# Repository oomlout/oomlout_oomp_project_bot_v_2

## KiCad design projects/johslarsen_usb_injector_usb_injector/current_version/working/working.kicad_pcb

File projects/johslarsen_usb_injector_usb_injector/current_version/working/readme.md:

# usb_injector
 
## summary 
* id: johslarsen_usb_injector_usb_injector
* user: johslarsen
* name: usb_injector
* board: usb_injector
* repo: https://github.com/johslarsen/usb_injector
* src_file_repo_kicad_pcb: usb_injector.kicad_pcb
* src_file_repo_kicad_pcb_link: https://github.com/johslarsen/usb_injector/tree/master/usb_injector.kicad_pcb

* src_file_repo_sch: usb_injector.sch
* src_file_repo_sch_link: https://github.com/johslarsen/usb_injector/tree/master/usb_injector.sch
* full details link: https://github.com/oomlout/oomlout_oomp_project_bot_v_2/tree/main/projects/johslarsen_usb_injector_usb_injector/current_version/working

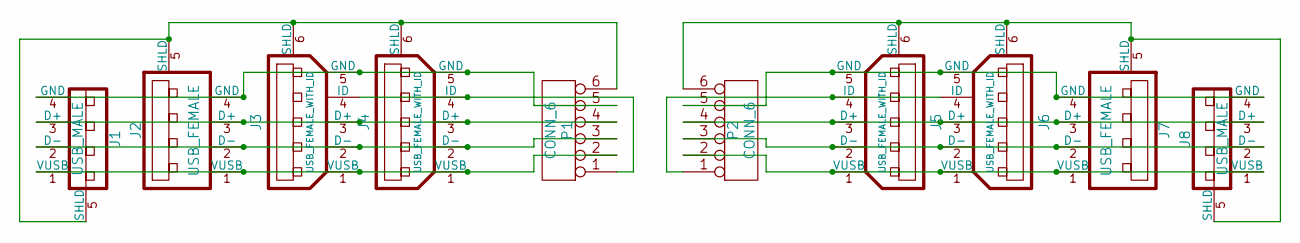
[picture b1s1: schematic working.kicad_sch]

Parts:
J1, J8: USB_MALE
J2, J7: USB_FEMALE
J3, J4, J5, J6: USB_FEMALE_WITH_ID
P1, P2: CONN_6

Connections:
unnamed: J1.1 (VUSB), J2.1 (VUSB), J3.1 (VUSB), J4.1 (VUSB), P1.2
unnamed: J1.2 (D-), J2.2 (D-), J3.2 (D-), J4.2 (D-), P1.3
unnamed: J1.3 (D+), J2.3 (D+), J3.3 (D+), J4.3 (D+), P1.4
unnamed: J1.4 (GND), J2.4 (GND), J3.5 (GND), J4.5 (GND), P1.5
unnamed: J1.5 (SHLD), J2.5 (SHLD), J3.6 (SHLD), J4.6 (SHLD), P1.6
unnamed: J3.4 (ID), J4.4 (ID), P1.1
unnamed: J5.1 (VUSB), J6.1 (VUSB), J7.1 (VUSB), J8.1 (VUSB), P2.2
unnamed: J5.2 (D-), J6.2 (D-), J7.2 (D-), J8.2 (D-), P2.3
unnamed: J5.3 (D+), J6.3 (D+), J7.3 (D+), J8.3 (D+), P2.4
unnamed: J5.4 (ID), J6.4 (ID), P2.1
unnamed: J5.5 (GND), J6.5 (GND), J7.4 (GND), J8.4 (GND), P2.5
unnamed: J5.6 (SHLD), J6.6 (SHLD), J7.5 (SHLD), J8.5 (SHLD), P2.6

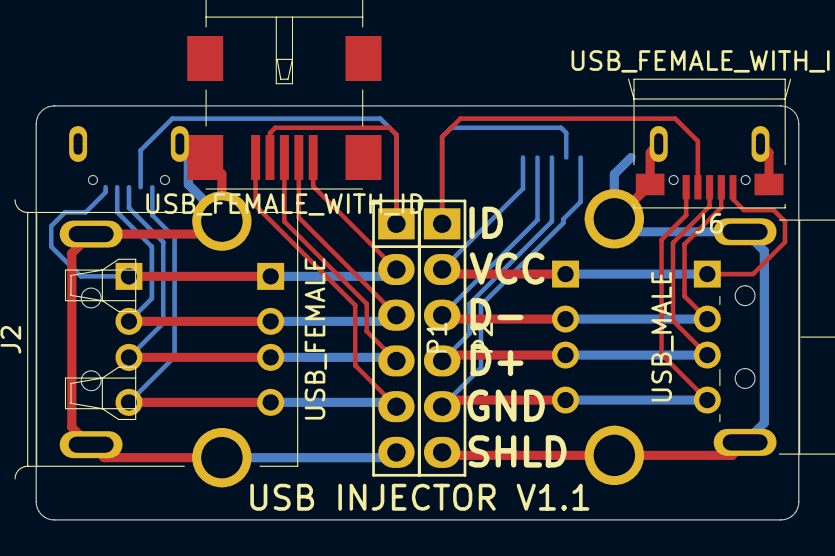
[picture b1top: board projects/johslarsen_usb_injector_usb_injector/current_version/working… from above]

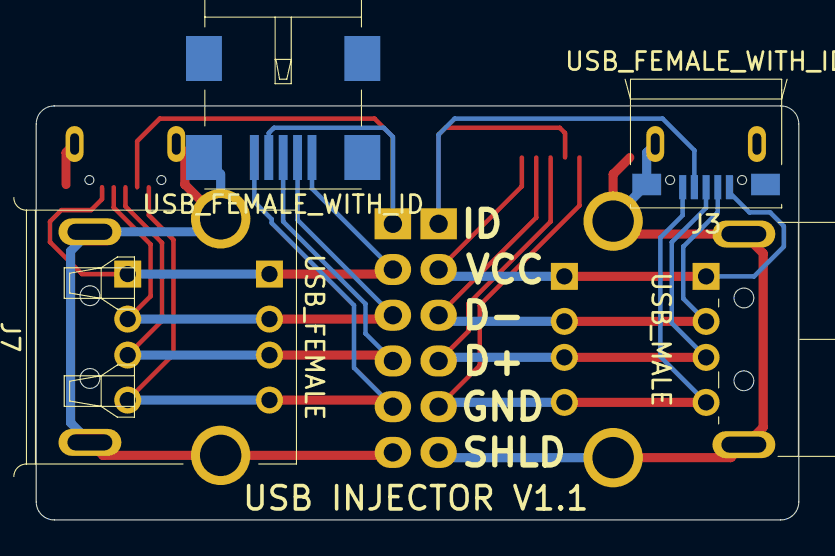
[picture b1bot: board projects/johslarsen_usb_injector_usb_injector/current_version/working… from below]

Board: 2 copper layers, 42.4 x 23.0 mm, 10 parts (4 on the bottom side), 12 nets.

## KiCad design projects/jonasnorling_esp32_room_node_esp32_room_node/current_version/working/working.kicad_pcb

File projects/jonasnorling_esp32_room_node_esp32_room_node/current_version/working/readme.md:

# esp32_room_node
 
## summary 
* id: jonasnorling_esp32_room_node_esp32_room_node
* user: jonasnorling
* name: esp32_room_node
* board: esp32_room_node
* repo: https://github.com/JonasNorling/esp32_room_node
* src_file_repo_kicad_pcb: hw/esp32_room_node.kicad_pcb
* src_file_repo_kicad_pcb_link: https://github.com/JonasNorling/esp32_room_node/tree/main/hw/esp32_room_node.kicad_pcb

* src_file_repo_sch: hw/esp32_room_node.sch
* src_file_repo_sch_link: https://github.com/JonasNorling/esp32_room_node/tree/main/hw/esp32_room_node.sch
* full details link: https://github.com/oomlout/oomlout_oomp_project_bot_v_2/tree/main/projects/jonasnorling_esp32_room_node_esp32_room_node/current_version/working

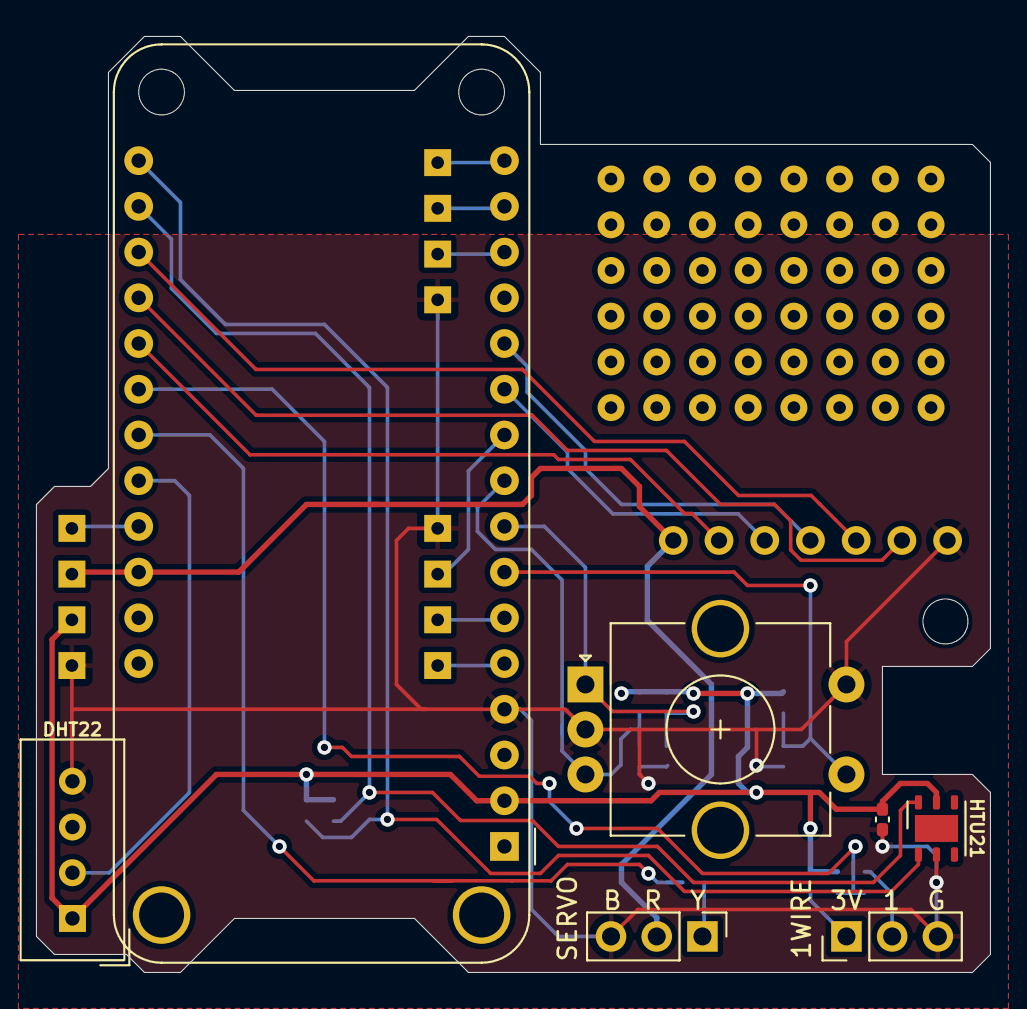
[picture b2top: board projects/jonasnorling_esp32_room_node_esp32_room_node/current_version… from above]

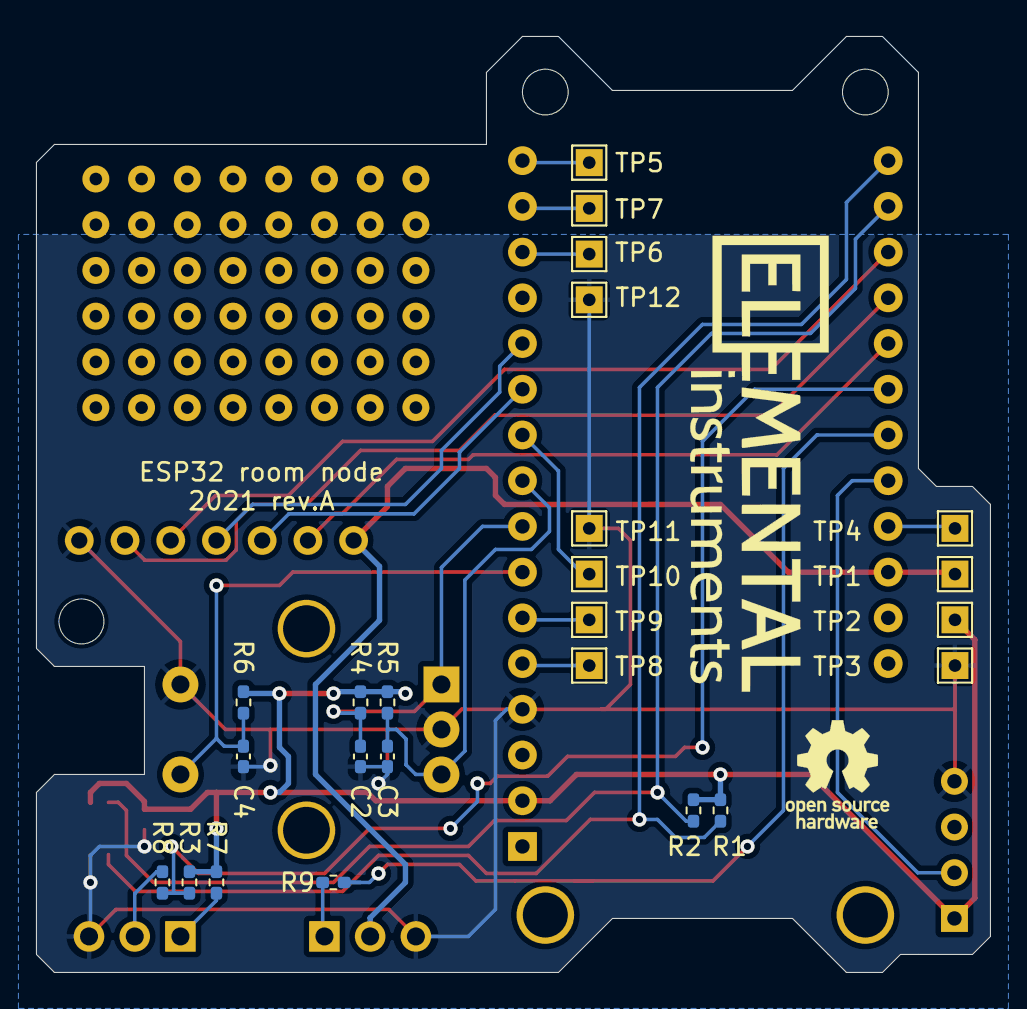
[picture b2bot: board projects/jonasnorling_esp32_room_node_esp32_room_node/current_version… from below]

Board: 2 copper layers, 53.0 x 52.0 mm, 37 parts (26 on the bottom side), 26 nets.

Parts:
A1: Adafruit_Feather_HUZZAH32_ESP32; Adafruit_Feather_WithMountingHoles
C1: 100n; C_0402_1005Metric_Pad0.74x0.62mm_HandSolder
C2, C3, C4: DNP; C_0402_1005Metric_Pad0.74x0.62mm_HandSolder
DISP1: SPI LCD; PIM436
H1: MountingHole; MountingHole_2.5mm
J1, J2: Conn_01x03; PinHeader_1x03_P2.54mm_Vertical
LOGO1: Logo_Open_Hardware_Small; OSHW-Logo_5.7x6mm_SilkScreen
LOGO2: Logo_Open_Hardware_Small; elemental-4mm-mask
LOGO3: Logo_Open_Hardware_Small; elemental-25.4mm
PROTOAREA1: Logo_Open_Hardware_Small; protoarea
R1, R2, R4, R5, R6: R; R_0402_1005Metric_Pad0.72x0.64mm_HandSolder
R3: 4k7; R_0402_1005Metric_Pad0.72x0.64mm_HandSolder
R7, R8, R9: 10; R_0402_1005Metric_Pad0.72x0.64mm_HandSolder
SW1: Rotary_Encoder_Switch; RotaryEncoder_Alps_EC11E-Switch_Vertical_H20mm_CircularMoun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
TP1, TP2, TP3, TP4, TP5, TP6, TP7, TP8, TP9, TP10, TP11, TP12: TestPoint; TestPoint_THTPad_1.5x1.5mm_Drill0.7mm
U1: DHT11; Aosong_DHT11_5.5x12.0_P2.54mm
U2: HTU21; DFN-6-1EP_3x3mm_P1mm_EP1.5x2.4mm

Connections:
+3V3: A1.2, C1.1, R1.1, R2.1, R3.1, R4.1, R5.1, R6.1, R7.2, TP2.1, U1.1, U2.5
+5V: A1.26, DISP1.1, J2.2, TP1.1
/ENC_A: A1.8, C2.1, R4.2, SW1.A
/ENC_B: A1.9, C3.1, R5.2, SW1.B
/ENC_BTN: A1.7, C4.1, R6.2, SW1.S1
/LCD_BL: A1.20, DISP1.6
/LCD_CS: A1.21, DISP1.2
/LCD_DC: A1.19, DISP1.5
/LCD_MOSI: A1.12, DISP1.4
/LCD_SCK: A1.11, DISP1.3
/ONEWIRE: A1.22, R3.2, R8.2
/SCL: A1.18, R2.2, U2.6
/SDA: A1.17, R1.2, U2.1
/SENS_DATA: A1.24, U1.2
/SERVO: A1.23, R9.2
GND: A1.4, C1.2, C2.2, C3.2, C4.2, DISP1.7, J1.3, J2.3, SW1.C, SW1.S2, TP3.1, TP11.1, TP12.1, U1.4, U2.2
unnamed: A1.5, TP8.1
unnamed: A1.6, TP9.1
unnamed: A1.10, TP10.1
unnamed: A1.14, TP6.1
unnamed: A1.15, TP7.1
unnamed: A1.16, TP5.1
unnamed: A1.25, TP4.1
unnamed: J1.1, R7.1
unnamed: J1.2, R8.1
unnamed: J2.1, R9.1

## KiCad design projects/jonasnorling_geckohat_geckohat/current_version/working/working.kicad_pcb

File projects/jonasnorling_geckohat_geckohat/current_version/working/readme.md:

# geckohat
 
## summary 
* id: jonasnorling_geckohat_geckohat
* user: jonasnorling
* name: geckohat
* board: geckohat
* repo: https://github.com/JonasNorling/geckohat
* src_file_repo_kicad_pcb: geckohat.kicad_pcb
* src_file_repo_kicad_pcb_link: https://github.com/JonasNorling/geckohat/tree/master/geckohat.kicad_pcb

* src_file_repo_sch: geckohat.sch
* src_file_repo_sch_link: https://github.com/JonasNorling/geckohat/tree/master/geckohat.sch
* full details link: https://github.com/oomlout/oomlout_oomp_project_bot_v_2/tree/main/projects/jonasnorling_geckohat_geckohat/current_version/working

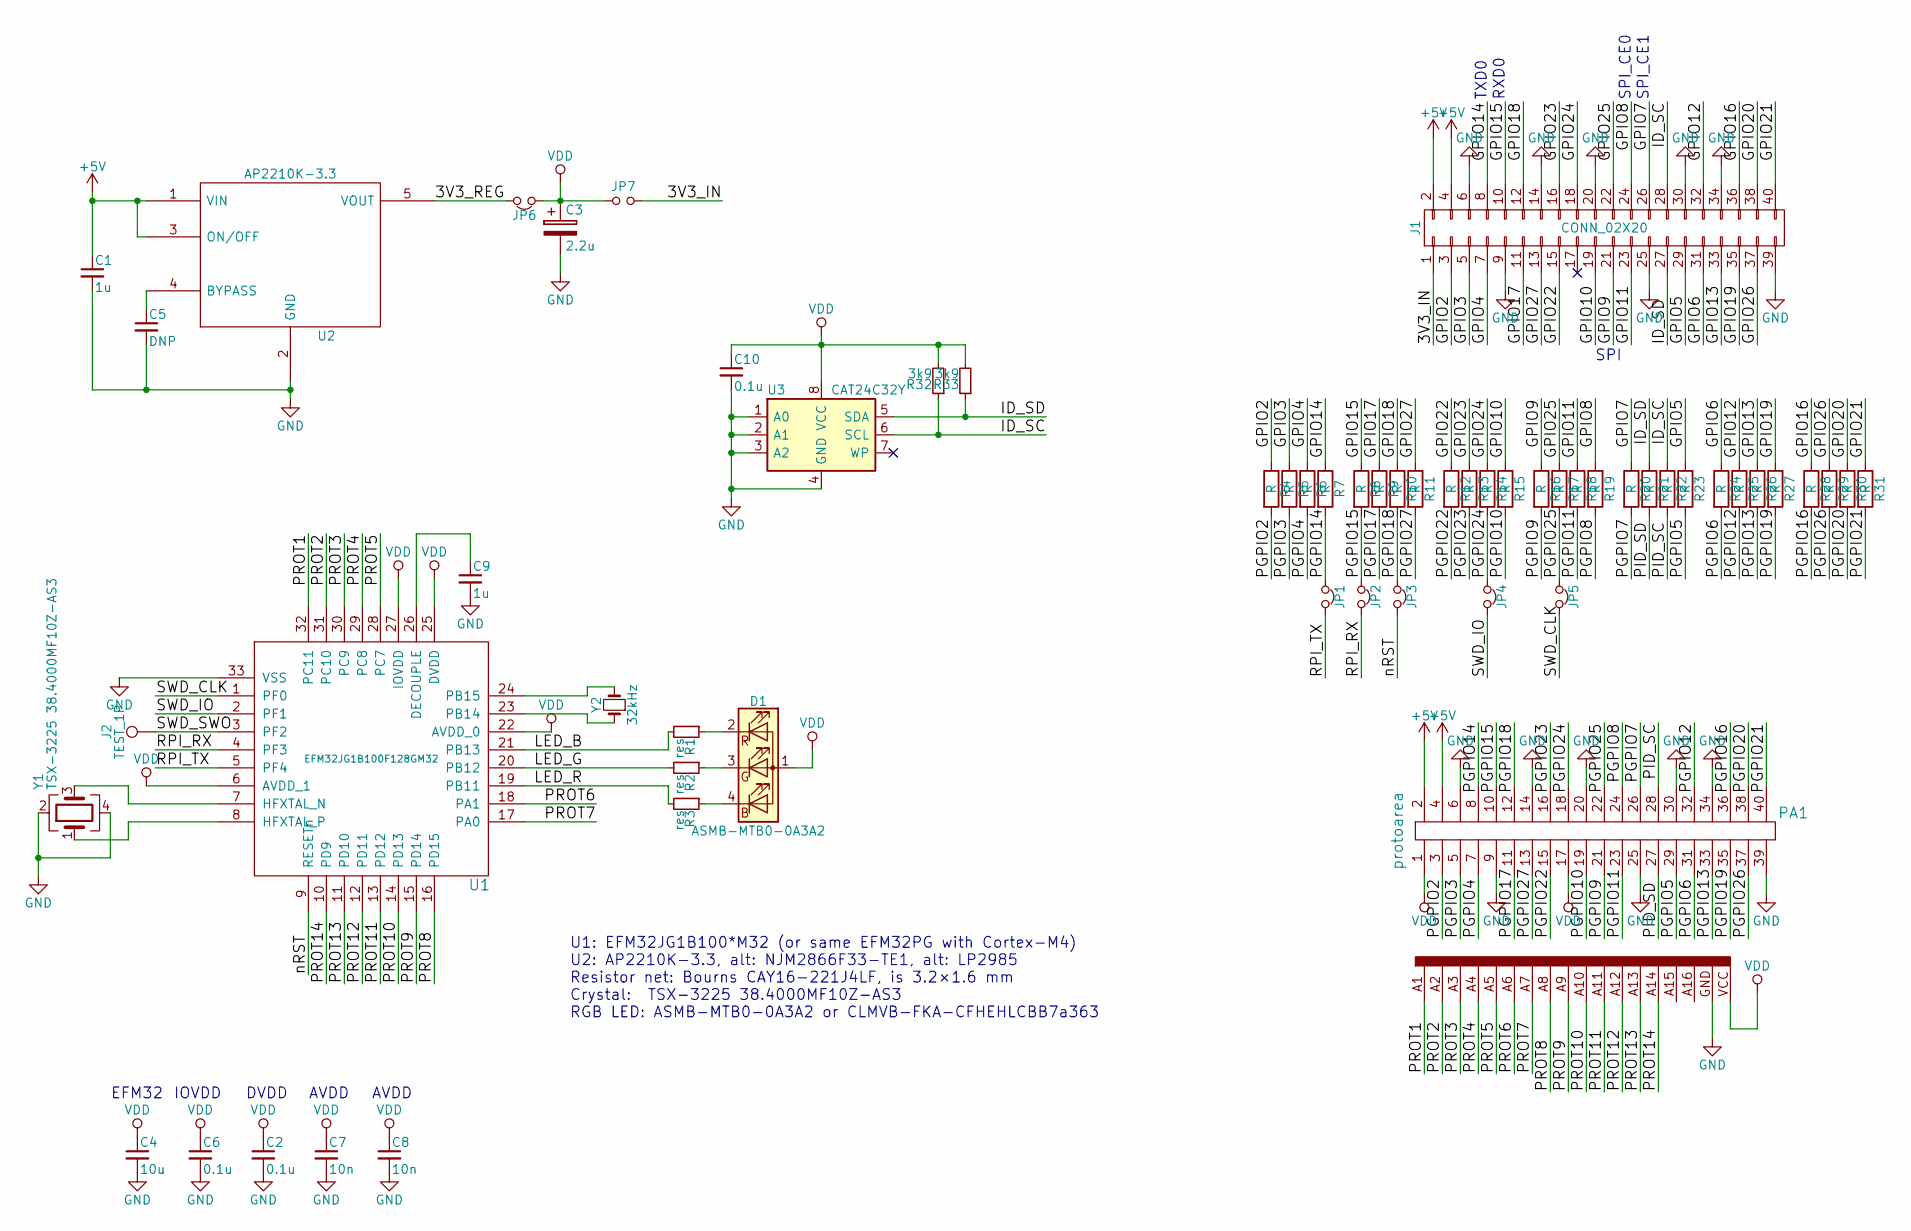
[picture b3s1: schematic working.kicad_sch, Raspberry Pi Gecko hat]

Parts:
C1, C9: 1u; C_0603_1608Metric_Pad0.84x1.00mm_HandSolder
C2, C6, C10: 0.1u; C_0603_1608Metric_Pad0.84x1.00mm_HandSolder
C3: 2.2u; C_0603_1608Metric_Pad0.84x1.00mm_HandSolder
C4: 10u; C_1206_3216Metric_Pad1.24x1.80mm_HandSolder
C5: DNP; C_0603_1608Metric_Pad0.84x1.00mm_HandSolder
C7, C8: 10n; C_0603_1608Metric_Pad0.84x1.00mm_HandSolder
D1: ASMB-MTB0-0A3A2; LED_Avago_PLCC4_3.2x2.8mm_CW
J1: CONN_02X20; Pin_Header_Straight_2x20_Pitch2.54mm
J2: TEST_1P; SolderWirePad_single_1mmDrill
JP1, JP2, JP3, JP4, JP5, JP6: tie; tie_0603
JP7: Jumper_NO_Small; tie_0603_open
PA1: protoarea
R1, R2, R3: res; R_0603_1608Metric_Pad0.84x1.00mm_HandSolder
R4, R5, R6, R7, R8, R9, R10, R11, R12, R13, R14, R15, R16, R17, R18, R19, R20, R21, R22, R23, R24, R25, R26, R27, R28, R29, R30, R31: R; R_0603_1608Metric_Pad0.84x1.00mm_HandSolder
R32, R33: 3k9; R_0603_1608Metric_Pad0.84x1.00mm_HandSolder
U1: EFM32JG1B100F128GM32; QFN-32-handsolder
U2: AP2210K-3.3; SOT-23-5_HandSoldering
U3: CAT24C32Y; TSSOP-8_4.4x3mm_Pitch0.65mm
Y1: TSX-3225 38.4000MF10Z-AS3; Crystal_SMD_SeikoEpson_FA238-4pin_3.2x2.5mm_HandSoldering
Y2: 32kHz; Crystal_C26-LF_d2.1mm_l6.5mm_Vertical

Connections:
+5V: C1.1, J1.2, J1.4, PA1.2, PA1.4, U2.1 (VIN), U2.3 (ON/OFF)
/3V3_IN: J1.1, JP7.2
/3V3_REG: JP6.2, U2.5 (VOUT)
/GPIO2: J1.3, R4.1
/GPIO3: J1.5, R5.1
/GPIO4: J1.7, R6.1
/GPIO5: J1.29, R23.1
/GPIO6: J1.31, R24.1
/GPIO7: J1.26, R20.1
/GPIO8: J1.24, R19.1
/GPIO9: J1.21, R16.1
/GPIO10: J1.19, R15.1
/GPIO11: J1.23, R18.1
/GPIO12: J1.32, R25.1
/GPIO13: J1.33, R26.1
/GPIO14: J1.8, R7.1
/GPIO15: J1.10, R8.1
/GPIO16: J1.36, R28.1
/GPIO17: J1.11, R9.1
/GPIO18: J1.12, R10.1
/GPIO19: J1.35, R27.1
/GPIO20: J1.38, R30.1
/GPIO21: J1.40, R31.1
/GPIO22: J1.15, R12.1
/GPIO23: J1.16, R13.1
/GPIO24: J1.18, R14.1
/GPIO25: J1.22, R17.1
/GPIO26: J1.37, R29.1
/GPIO27: J1.13, R11.1
/ID_SC: J1.28, R22.1, R32.1, U3.6 (SCL)
/ID_SD: J1.27, R21.1, R33.1, U3.5 (SDA)
/LED_B: R1.2, U1.21 (PB13)
/LED_G: R2.2, U1.20 (PB12)
/LED_R: R3.2, U1.19 (PB11)
/PGPIO2: PA1.3, R4.2
/PGPIO3: PA1.5, R5.2
/PGPIO4: PA1.7, R6.2
/PGPIO5: PA1.29, R23.2
/PGPIO6: PA1.31, R24.2
/PGPIO7: PA1.26, R20.2
/PGPIO8: PA1.24, R19.2
/PGPIO9: PA1.21, R16.2
/PGPIO10: PA1.19, R15.2
/PGPIO11: PA1.23, R18.2
/PGPIO12: PA1.32, R25.2
/PGPIO13: PA1.33, R26.2
/PGPIO14: JP1.1, PA1.8, R7.2
/PGPIO15: JP2.1, PA1.10, R8.2
/PGPIO16: PA1.36, R28.2
/PGPIO17: PA1.11, R9.2
/PGPIO18: JP3.1, PA1.12, R10.2
/PGPIO19: PA1.35, R27.2
/PGPIO20: PA1.38, R30.2
/PGPIO21: PA1.40, R31.2
/PGPIO22: PA1.15, R12.2
/PGPIO23: PA1.16, R13.2
/PGPIO24: JP4.1, PA1.18, R14.2
/PGPIO25: JP5.1, PA1.22, R17.2
/PGPIO26: PA1.37, R29.2
/PGPIO27: PA1.13, R11.2
/PID_SC: PA1.28, R22.2
/PID_SD: PA1.27, R21.2
/PROT1: PA1.A1, U1.32 (PC11)
/PROT2: PA1.A2, U1.31 (PC10)
/PROT3: PA1.A3, U1.30 (PC9)
/PROT4: PA1.A4, U1.29 (PC8)
/PROT5: PA1.A5, U1.28 (PC7)
/PROT6: PA1.A6, U1.18 (PA1)
/PROT7: PA1.A7, U1.17 (PA0)
/PROT8: PA1.A8, U1.16 (PD15)
/PROT9: PA1.A9, U1.15 (PD14)
/PROT10: PA1.A10, U1.14 (PD13)
/PROT11: PA1.A11, U1.13 (PD12)
/PROT12: PA1.A12, U1.12 (PD11)
/PROT13: PA1.A13, U1.11 (PD10)
/PROT14: PA1.A14, U1.10 (PD9)
/RPI_RX: JP2.2, U1.4 (PF3)
/RPI_TX: JP1.2, U1.5 (PF4)
/SWD_CLK: JP5.2, U1.1 (PF0)
/SWD_IO: JP4.2, U1.2 (PF1)
/SWD_SWO: J2.1, U1.3 (PF2)
/nRST: JP3.2, U1.9 (RESETn)
GND: C1.2, C2.2, C3.2, C4.2, C5.2, C6.2, C7.2, C8.2, C9.2, C10.2, J1.6, J1.9, J1.14, J1.20, J1.25, J1.30, J1.34, J1.39, PA1.6, PA1.9, PA1.14, PA1.20, PA1.25, PA1.30, PA1.34, PA1.39, PA1.GND, U1.33 (VSS), U2.2 (GND), U3.1 (A0), U3.2 (A1), U3.3 (A2), U3.4 (GND), Y1.2, Y1.4
unnamed: C5.1, U2.4 (BYPASS)
unnamed: C9.1, U1.26 (DECOUPLE)
unnamed: D1.2 (RK), R1.1
unnamed: D1.3 (GK), R2.1
unnamed: D1.4 (BK), R3.1
unnamed: U1.7 (HFXTAL_N), Y1.3
unnamed: U1.8 (HFXTAL_P), Y1.1
unnamed: U1.23 (PB14), Y2.1
unnamed: U1.24 (PB15), Y2.2
VDD: C2.1, C3.1, C4.1, C6.1, C7.1, C8.1, C10.1, D1.1 (A), JP6.1, JP7.1, PA1.1, PA1.17, PA1.VCC, R32.2, R33.2, U1.6 (AVDD_1), U1.22 (AVDD_0), U1.25 (DVDD), U1.27 (IOVDD), U3.8 (VCC)

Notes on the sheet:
SPI_CE0
TXD0
IOVDD
EFM32
AVDD
RXD0
DVDD
U1: EFM32JG1B100*M32 (or same EFM32PG with Cortex-M4) U2: AP2210K-3.3, alt: NJM2866F33-TE1, alt: LP2985 Resistor net: Bourns CAY16-221J4LF, is 3.2×1.6 mm Crystal: TSX-3225 38.4000MF10Z-AS3 RGB LED: ASMB-MTB0-0A3A2 or CLMVB-FKA-CFHEHLCBB7a363
SPI_CE1
SPI

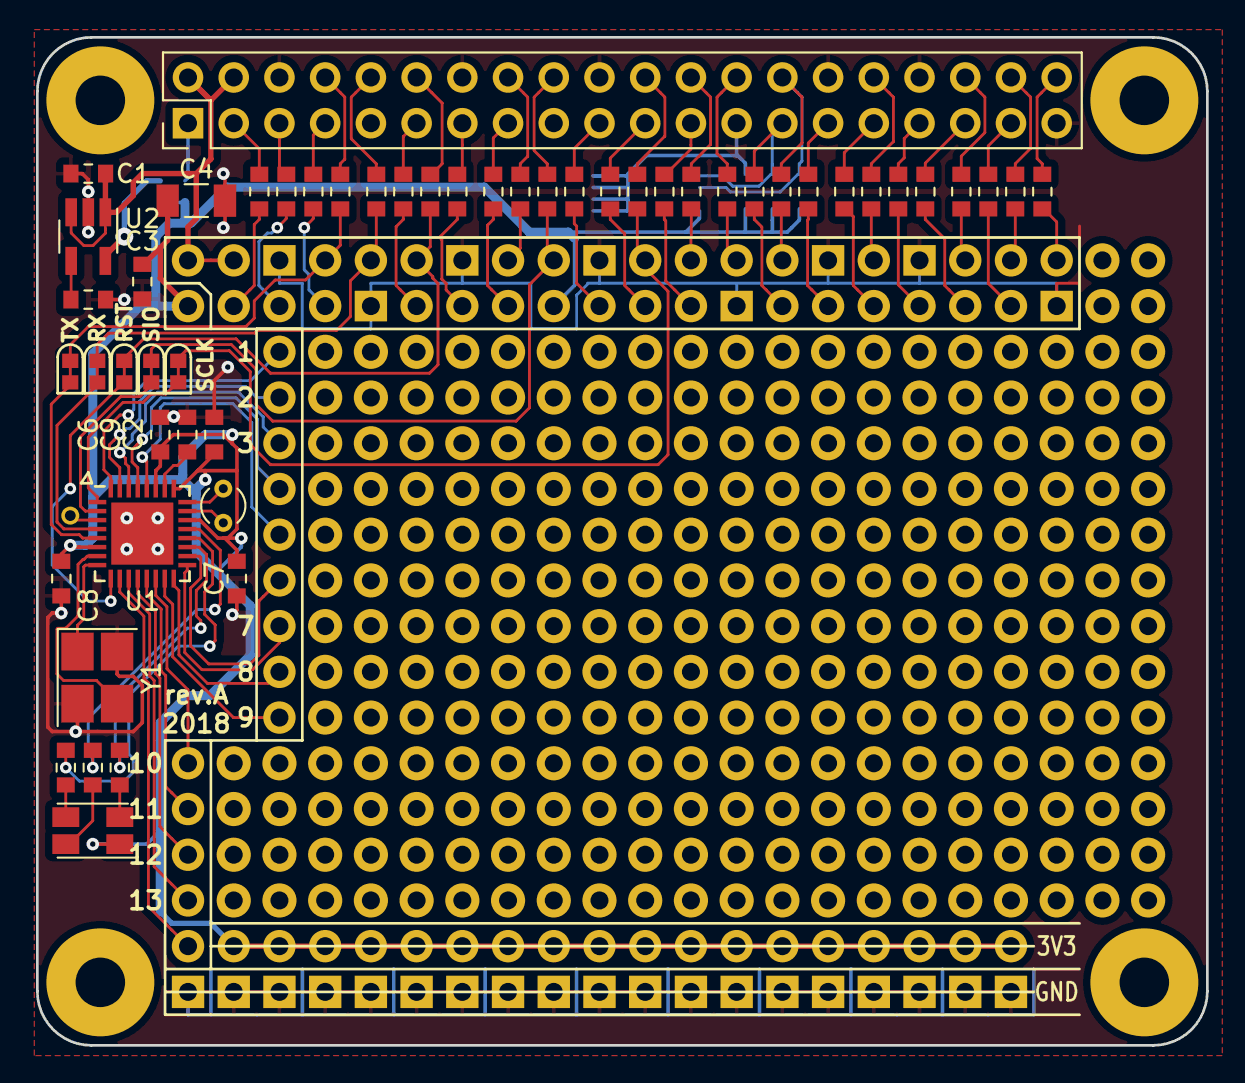
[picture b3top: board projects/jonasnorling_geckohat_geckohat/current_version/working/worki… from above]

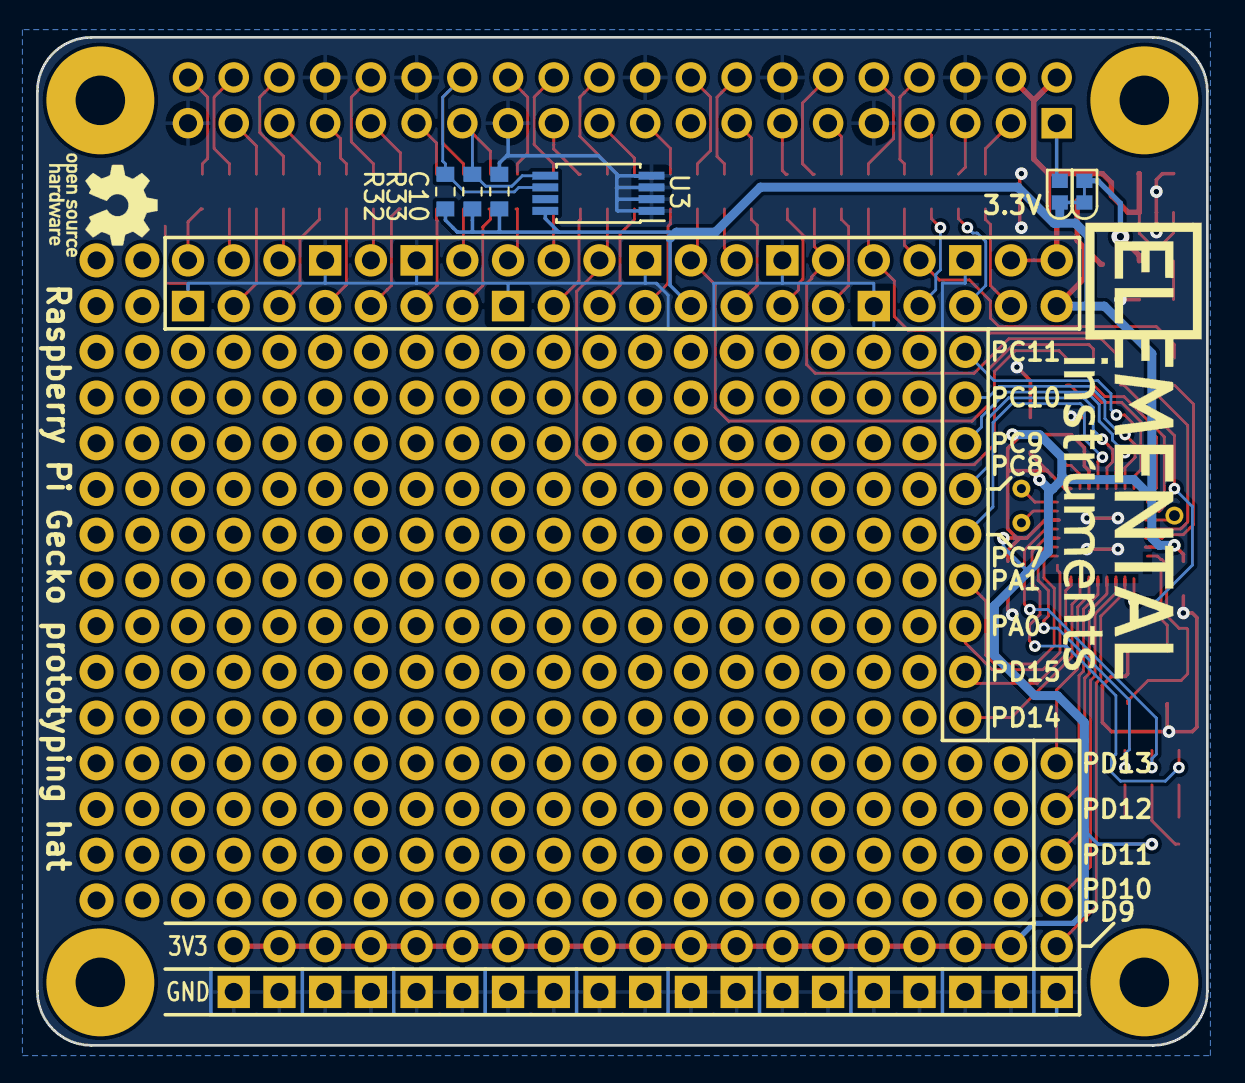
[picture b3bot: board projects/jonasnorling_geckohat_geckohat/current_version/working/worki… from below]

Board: 2 copper layers, 65.0 x 56.0 mm, 59 parts (6 on the bottom side), 93 nets.

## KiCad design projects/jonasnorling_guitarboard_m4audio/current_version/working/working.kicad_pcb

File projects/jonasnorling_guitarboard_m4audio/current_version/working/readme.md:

# guitarboard
 
## summary 
* id: jonasnorling_guitarboard_m4audio
* user: jonasnorling
* name: guitarboard
* board: m4audio
* repo: https://github.com/JonasNorling/guitarboard
* src_file_repo_kicad_pcb: hw/m4audio.kicad_pcb
* src_file_repo_kicad_pcb_link: https://github.com/JonasNorling/guitarboard/tree/master/hw/m4audio.kicad_pcb

* src_file_repo_sch: 
* src_file_repo_sch_link: https://github.com/JonasNorling/guitarboard/tree/master/
* full details link: https://github.com/oomlout/oomlout_oomp_project_bot_v_2/tree/main/projects/jonasnorling_guitarboard_m4audio/current_version/working

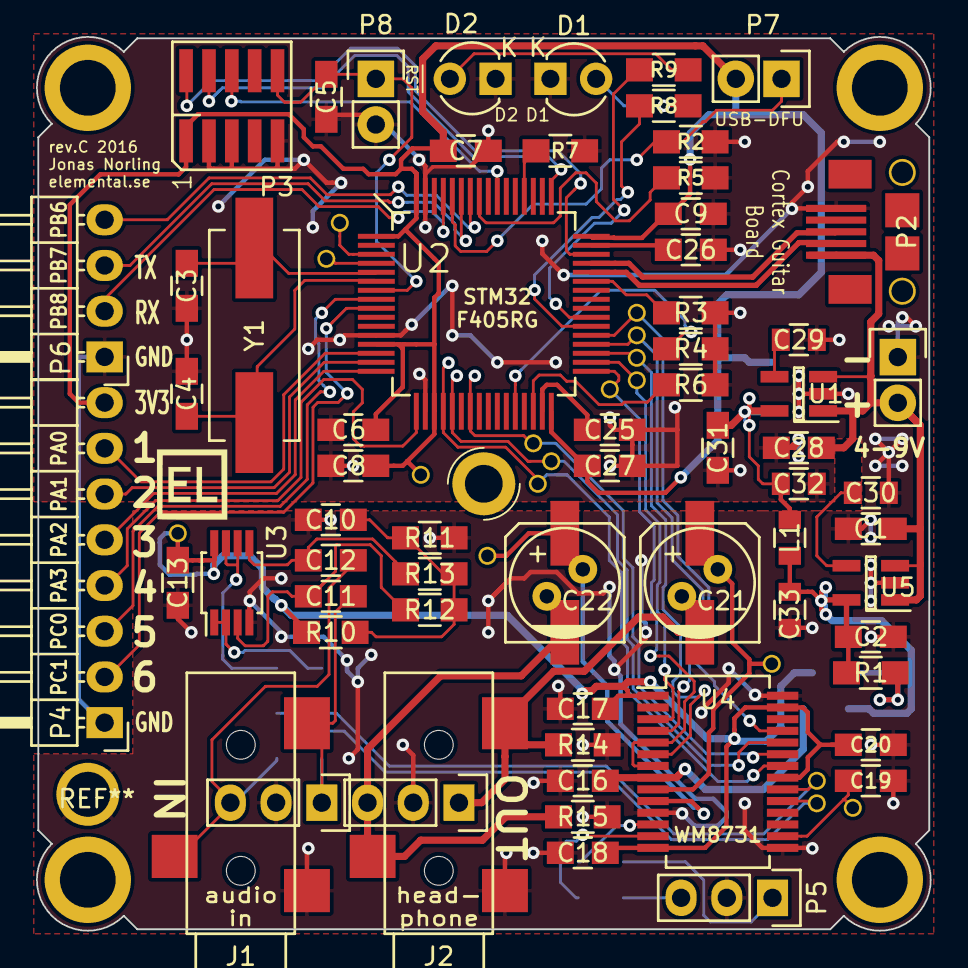
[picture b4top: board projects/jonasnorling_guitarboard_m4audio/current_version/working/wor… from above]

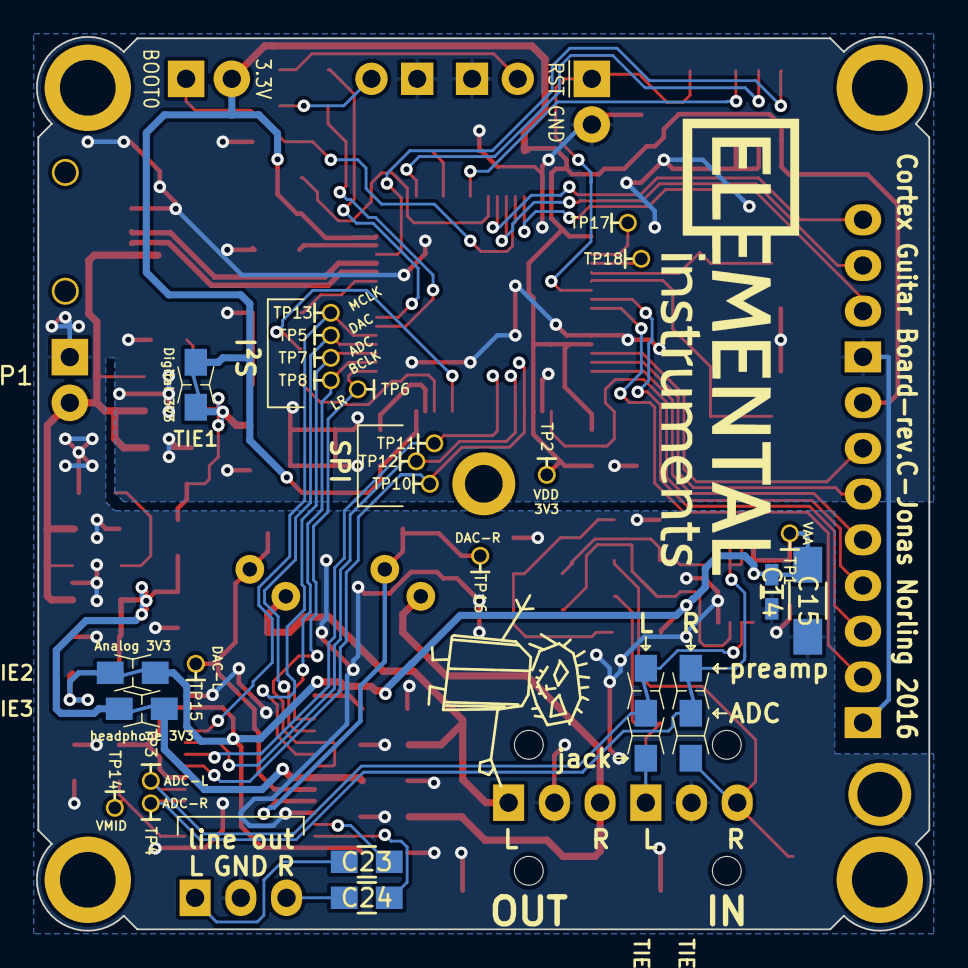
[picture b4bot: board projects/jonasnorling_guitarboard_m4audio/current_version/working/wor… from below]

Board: 2 copper layers, 49.7 x 49.7 mm, 91 parts (26 on the bottom side), 67 nets.

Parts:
C1, C28: 10u16V; C_0805_HandSoldering
C2, C10, C13, C16, C17, C18, C19, C20, C31: 10u; C_0805_HandSoldering
C3, C4: 27p; C_0805_HandSoldering
C5, C7, C8, C9, C11, C12, C27: 100n; C_0805_HandSoldering
C6: 1u; C_0805_HandSoldering
C14: DNP; C_0603_HandSoldering
C15: DNP; C_1206_HandSoldering
C21, C22: 220u; c_elec_6.3x7.7
C23, C24: DNP; C_0805_HandSoldering
C25, C26: 2.2u; C_0805_HandSoldering
C29, C30, C32, C33: DNP; C_0805
D1: green; LED-3MM
D2: orange; LED-3MM
J1, J2: JACK_TRS; 35RASMT2BHNTRX
J11, J21: CONN_01X03; Pin_Header_Straight_1x03
L1: DNP; C_0805
P1, P7, P8: CONN_01X02; Pin_Header_Straight_1x02
P2: USB_OTG; USB_Micro_FCI
P3: CONN_02X05; Pin_Header_SMT_1.27_2x5
P4: CONN_01X08; Pin_Header_Angled_1x08
P5: CONN_01X03; Pin_Header_Straight_1x03
P6: CONN_01X04; Pin_Header_Angled_1x04
R1: 10; R_0805_HandSoldering
R2, R3, R4, R5, R6, R7, R10, R11, R14, R15: 100k; R_0805_HandSoldering
R8, R9: 470; R_0805_HandSoldering
R12, R13: 560k; R_0805_HandSoldering
TIE1: V_D; net_tie_0805
TIE2: V_A; net_tie_0805
TIE3: V_HP; net_tie_0805
TIE4, TIE5: CONN_01X03; net_tie_3_0805
TP1, TP2, TP3, TP4, TP5, TP6, TP7, TP8, TP10, TP11, TP12, TP13, TP14, TP15, TP16, TP17, TP18: TST; TP_0.7mm
U1, U5: AP2210K-3.3; SOT-23-5_Handsoldering
U2: STM32F405RG; QFP50P1200X1200-64
U3: MCP6002; MSOP-8_3x3mm_Pitch0.65mm
U4: WM8731; SSOP-28_5.3x10.2mm_Pitch0.65mm
Y1: 8MHz; Crystal_HC49-SD_SMD

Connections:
/APWR: C2.1, C33.1, L1.1, R1.1, TIE3.2, U5.5
/BOOT0: P7.1, R2.2, U2.60
/BOOT1: R4.2, U2.28
/BYP1: C29.1, U1.4
/BYP2: C30.1, U5.4
/DPWR: C31.1, C32.2, L1.2, TIE1.2, U1.5
/LED1: R8.2, U2.38
/LED2: R9.2, U2.39
/MISC1: P4.7, U2.14
/MISC2: P4.6, U2.15
/MISC3: P4.5, U2.16
/MISC4: P4.4, U2.17
/MISC5: P4.3, U2.8
/MISC6: P4.2, U2.9
/NRST: C5.1, P3.10, P8.1, U2.7
/OSCIN: C3.1, U2.5, Y1.1
/OSCOUT: C4.1, U2.6, Y1.2
/PB6: P6.4, U2.58
/PB7: P6.3, U2.59
/PB8: P6.2, U2.61
/PWR_5V: C1.1, C28.1, P1.2, P2.1, U1.1, U1.3, U5.1, U5.3
/SWCLK: P3.4, U2.49
/SWDIO: P3.2, U2.46
/SWO: P3.6, U2.55
/USB_DM: P2.2, U2.44
/USB_DP: P2.3, U2.45
/VCAP1: C25.1, U2.31
/VCAP2: C26.1, U2.47
/audio/ADCDAT: TP7.1, U2.35, U4.6
/audio/ADCL: TIE4.2, TP3.1, U4.20
/audio/ADCLR: TP6.1, U2.33, U4.5, U4.7
/audio/ADCR: TIE5.2, TP4.1, U4.19
/audio/AIN_L: C11.2, J1.2, J11.1, TIE4.3
/audio/AIN_R: C12.2, J1.3, J11.3, TIE5.3
/audio/AOUT_L: C21.2, J2.2, J21.1, R14.1
/audio/AOUT_R: C22.2, J2.3, J21.3, R15.1
/audio/BCLK: TP8.1, U2.34, U4.3
/audio/CS: TP10.1, U2.20, U4.22
/audio/DACDAT: TP5.1, U2.36, U4.4
/audio/DACL: C21.1, TP15.1, U4.9
/audio/DACR: C22.1, TP16.1, U4.10
/audio/LINEL: C23.1, U4.12
/audio/LINER: C24.1, U4.13
/audio/MCLK: TP13.1, U2.37, U4.25
/audio/MOSI: TP11.1, U2.23, U4.23
/audio/OPINL: C11.1, R12.2, U3.3
/audio/OPINR: C12.1, R13.1, U3.5
/audio/OPOUTL: TIE4.1, U3.1, U3.2
/audio/OPOUTR: TIE5.1, U3.6, U3.7
/audio/SCLK: TP12.1, U2.21, U4.24
/audio/VMID: C19.2, TP14.1, U4.16
/audio/bias: C10.2, R10.1, R11.2, R12.1, R13.2
GND: C1.2, C2.2, C3.2, C4.2, C5.2, C6.2, C7.2, C8.2, C9.2, C10.1, C13.1, C14.1, C15.1, C16.1, C17.1, C18.1, C19.1, C20.1, C25.2, C26.2, C27.2, C28.2, C29.2, C30.2, C31.2, C32.1, C33.2, D1.1, D2.1, J1.1, J2.1, J11.2, J21.2, P1.1, P2.5, P3.3, P3.5, P3.9, P4.1, P5.2, P6.1, P8.2, R2.1, R3.2, R4.1, R5.1, R6.1, R7.1, R11.1, R14.2, R15.2, U1.2, U2.12, U2.18, U2.63, U3.4, U4.11, U4.15, U4.28, U5.2
HPVDD: C16.2, TIE3.1, U4.8
unnamed: C23.2, P5.1
unnamed: C24.2, P5.3
unnamed: D1.2, R8.1
unnamed: D2.2, R9.1
unnamed: R1.2, TIE2.2
unnamed: R3.1, U2.43
unnamed: R5.2, U2.57
unnamed: R6.2, U2.30
unnamed: R7.2, U2.52
unnamed: TP17.1, U2.3
unnamed: TP18.1, U2.4
VAA: C13.2, C14.2, C15.2, C17.2, C18.2, C20.2, R10.2, TIE2.1, TP1.1, U3.8, U4.1, U4.14, U4.21, U4.27
VDD: C6.1, C7.1, C8.1, C9.1, C27.1, P3.1, P4.8, P7.2, TIE1.1, TP2.1, U2.1, U2.13, U2.19, U2.32, U2.48, U2.64

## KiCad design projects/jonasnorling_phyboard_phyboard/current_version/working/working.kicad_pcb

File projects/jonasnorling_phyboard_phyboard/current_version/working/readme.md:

# phyboard
 
## summary 
* id: jonasnorling_phyboard_phyboard
* user: jonasnorling
* name: phyboard
* board: phyboard
* repo: https://github.com/JonasNorling/phyboard
* src_file_repo_kicad_pcb: phyboard-rotated.kicad_pcb
* src_file_repo_kicad_pcb_link: https://github.com/JonasNorling/phyboard/tree/master/phyboard-rotated.kicad_pcb

* src_file_repo_sch: 
* src_file_repo_sch_link: https://github.com/JonasNorling/phyboard/tree/master/
* full details link: https://github.com/oomlout/oomlout_oomp_project_bot_v_2/tree/main/projects/jonasnorling_phyboard_phyboard/current_version/working

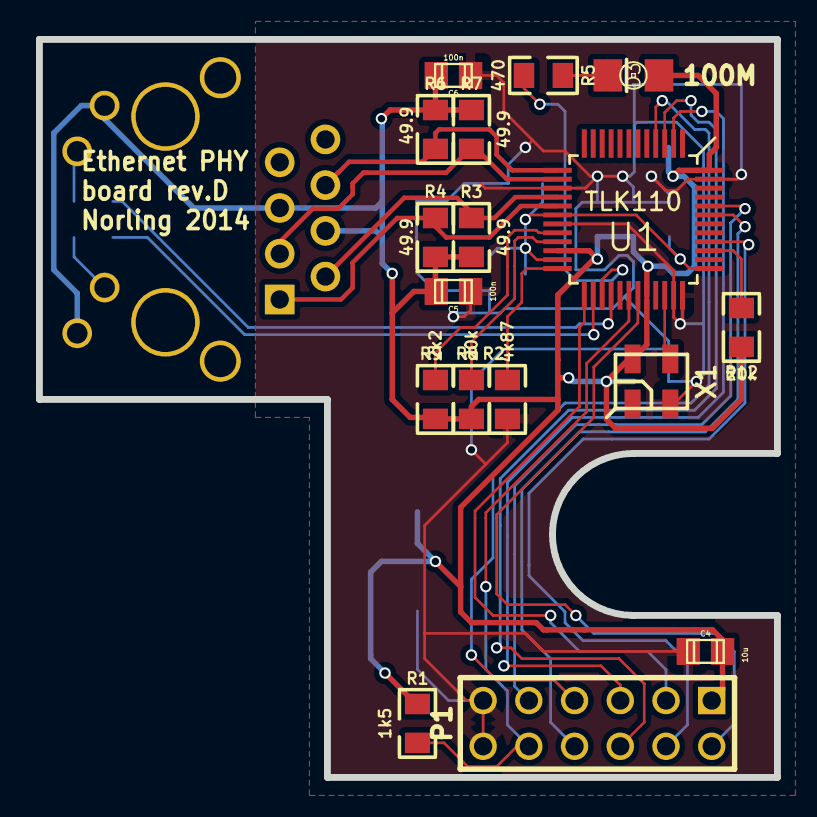
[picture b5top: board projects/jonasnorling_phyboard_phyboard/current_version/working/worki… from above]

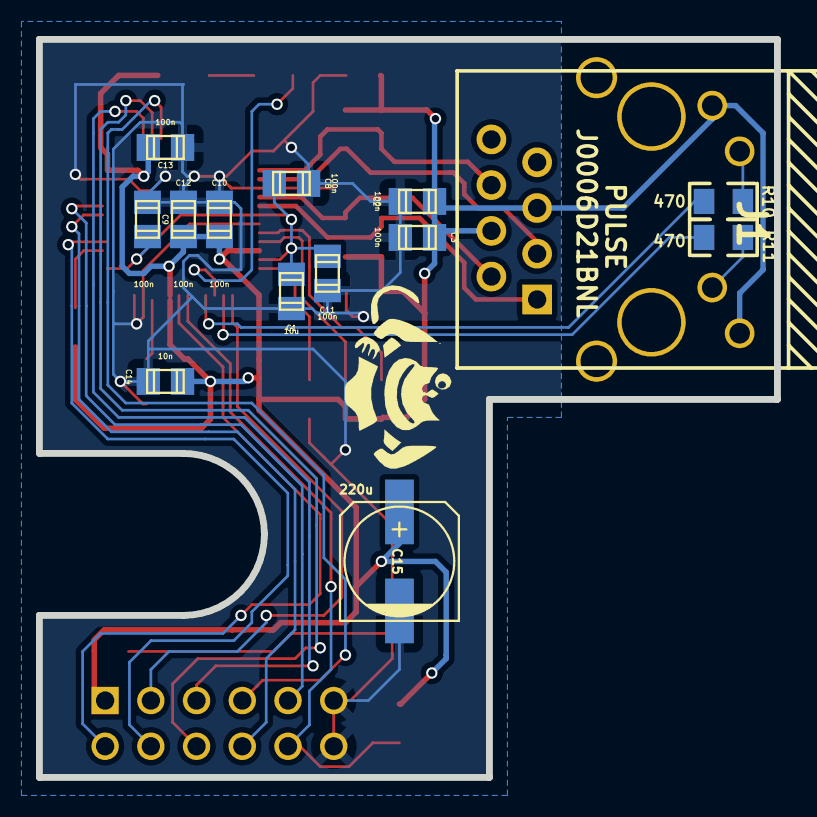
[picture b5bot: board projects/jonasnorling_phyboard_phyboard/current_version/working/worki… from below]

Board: 2 copper layers, 41.0 x 41.0 mm, 31 parts (14 on the bottom side), 27 nets.

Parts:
C1, C4: 10u; c_0805
C2, C3, C5, C6, C8, C9, C10, C11, C12, C13: 100n; c_0805
C14: 10n; c_0805
C15: 220u; c_elec_6.3x5.3
D3: LED; LED-1206
J1: PULSE-J0006; pulse-J0006D21BNL
P1: CONN_6X2; pin_array_6x2
R1: 1k5; SM0805-jonas
R2: 4k87; SM0805-jonas
R3, R4, R6, R7: 49.9; SM0805-jonas
R5, R10, R11: 470; SM0805-jonas
R8, R12: 20k; SM0805-jonas
R9: 2k2; SM0805-jonas
U1: TLK110; QFP50P900X900-48M
X1: ASEMB-50.000MHZ-LC-T; oscillator-3.2x2.5

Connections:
+3.3V: C2.1, C3.1, C4.1, C5.1, C6.1, C10.1, C12.1, C13.1, C14.1, C15.1, D3.1, J1.4, J1.5, J1.9, J1.12, P1.1, R1.2, R3.1, R4.2, R6.1, R7.2, R8.2, R9.2, R12.2, U1.22, U1.32, U1.48, X1.4
/ETH_CLK: P1.3, U1.25
/ETH_CRS: P1.4, U1.40
/ETH_MDC: P1.2, U1.31
/ETH_MDIO: P1.10, R1.1, U1.30
/ETH_RxD0: P1.8, U1.43
/ETH_RxD1: P1.9, U1.44
/ETH_TX_EN: P1.5, U1.2
/ETH_TxD0: P1.6, U1.3
/ETH_TxD1: P1.7, U1.4
/LED1: J1.11, R10.2
/LED2: J1.10, R11.2
/LED3: D3.2, R5.2
/OSC: U1.34, X1.3
/PFB: C1.1, C8.1, C9.1, C11.1, U1.18, U1.23, U1.37
/RD+: J1.3, R7.1, U1.14
/RD-: J1.6, R6.2, U1.13
/RMII_MODE: R12.1, U1.39
/TD+: J1.1, R4.1, U1.17
/TD-: J1.2, R3.2, U1.16
GND: C1.2, C2.2, C3.2, C4.2, C5.2, C6.2, C8.2, C9.2, C10.2, C11.2, C12.2, C13.2, C14.2, C15.2, P1.11, P1.12, R2.2, U1.15, U1.19, U1.35, U1.36, U1.47, X1.2
unnamed: R2.1, U1.24
unnamed: R8.1, U1.21
unnamed: R9.1, U1.20
unnamed: R10.1, U1.28
unnamed: R5.1, U1.27
unnamed: R11.1, U1.26
